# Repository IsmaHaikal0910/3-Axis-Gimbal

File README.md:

# Camera Gimbal — 3-Axis Stabilization for Smartphones & Cameras

> Custom-built 3-axis camera gimbal (STorM32 BGC + ESP32) with a self-designed 3D-printed frame, wireless shutter control, and a web dashboard for battery/BLE monitoring. Built for a Mechatronics lab project at Jade University of Applied Sciences.

---

## 🇬🇧 English

### Overview
This project is a fully custom 3-axis camera gimbal for smartphones and small action cameras, developed as part of the "Komplexlabor Mechatronik" course at Jade Hochschule Wilhelmshaven (Summer 2026). The goal was to design, build, and validate a handheld gimbal that stabilizes roll, pitch, and yaw in real time, using a mechanically optimized 3D-printed frame and an open, configurable electronics stack instead of a proprietary commercial system (e.g. DJI RS5).

### Key Features
- **3-axis active stabilization** (roll, pitch, yaw) via three iPower GM3506 brushless gimbal motors with AS5048A encoders
- **STorM32 v4.1** BGC controller + **NT IMU v4.2** for orientation sensing and PID-based motor control
- **ESP32** microcontroller handling joystick input, buttons, status LED, and wireless connectivity
- **WLAN/Bluetooth bridge**: a companion phone connects to the ESP32 over Wi-Fi and relays Bluetooth shutter commands to the camera
- **Custom HTML web interface** showing live battery percentage/voltage and providing remote shutter + Bluetooth scan controls
- Self-designed 3D-printed frame (P430 ABS+), removable 11.1 V / 3000 mAh LiPo battery, IP54-rated enclosure target
- Requirements list, circuit diagram, energy-flow diagram, and full verification & validation (V&V) test protocol

### Test Results (summary)
| Test | Result |
|---|---|
| Battery life (215 g payload) | ~2 hours |
| Reaction time (90° step) | 2.46 s (≈36.6°/s) |
| IMU drift (roll/pitch) | No measurable drift |
| Motor thermal | Uncritical after 10–15 min continuous load |
| TRL | 4, approaching 5 |

### Hardware
STorM32 v4.1, NT IMU v4.2, 3× iPower GM3506 gimbal motors, ESP32 (NodeMCU), analog joystick module, 2-button module, RGB status LED, 11.1 V 3000 mAh LiPo + balance charger. Full bill of materials with suppliers and cost is included in the lab report.

### Status & Outlook
The mechanical and electrical integration is complete; PID tuning (especially on the yaw axis) and full closed-loop real-time stabilization are ongoing. Planned next steps include C++/PlatformIO code refactoring with auto-reconnect, mechanical load testing of the screw connections, and empirical battery-life validation under real load.

---

## 🇩🇪 Deutsch

### Überblick
Dieses Projekt ist ein vollständig selbst entwickeltes 3-Achsen-Kamera-Gimbal für Smartphones und kleine Actioncams, entstanden im Rahmen des Komplexlabors Mechatronik an der Jade Hochschule Wilhelmshaven (Sommersemester 2026). Ziel war die Konstruktion, der Aufbau und die Validierung eines Handheld-Gimbals, das Roll-, Pitch- und Yaw-Bewegungen in Echtzeit ausgleicht — mit einem mechanisch optimierten, selbst konstruierten 3D-Druck-Rahmen und einer offenen, konfigurierbaren Elektronik statt eines proprietären kommerziellen Systems (z. B. DJI RS5).

### Hauptmerkmale
- **Aktive 3-Achsen-Stabilisierung** (Roll, Pitch, Yaw) über drei bürstenlose iPower-GM3506-Kardanmotoren mit AS5048A-Encodern
- **STorM32 v4.1** BGC-Controller + **NT IMU v4.2** zur Lageerfassung und PID-basierten Motorregelung
- **ESP32**-Mikrocontroller für Joystick-Eingabe, Taster, Status-LED und drahtlose Kommunikation
- **WLAN/Bluetooth-Brücke**: Ein Mobiltelefon verbindet sich per WLAN mit dem ESP32 und leitet Bluetooth-Auslösebefehle an die Kamera weiter
- **Eigenes HTML-Web-Interface** mit Live-Anzeige von Akkustand/Spannung sowie Fernsteuerung von Auslöser und Bluetooth-Suchlauf
- Selbst konstruierter 3D-Druck-Rahmen (P430 ABS+), entnehmbarer 11,1 V / 3000 mAh LiPo-Akku, Gehäuse ausgelegt auf IP54
- Anforderungsliste, Schaltplan, Energieflussdiagramm sowie ein vollständiges Verifikations- und Validierungs-Testprotokoll (V+V)

### Testergebnisse (Zusammenfassung)
| Test | Ergebnis |
|---|---|
| Akkulaufzeit (215 g Nutzlast) | ca. 2 Stunden |
| Reaktionszeit (90°-Schwenk) | 2,46 s (≈36,6°/s) |
| IMU-Drift (Roll/Pitch) | Keine messbare Drift |
| Motorerwärmung | Unkritisch nach 10–15 Min Dauerbetrieb |
| TRL | 4, an der Schwelle zu 5 |

### Hardware
STorM32 v4.1, NT IMU v4.2, 3× iPower-GM3506-Kardanmotoren, ESP32 (NodeMCU), analoges Joystick-Modul, 2-Tasten-Modul, RGB-Status-LED, 11,1 V 3000 mAh LiPo-Akku mit Balance-Ladegerät. Die vollständige Stückliste mit Lieferanten und Kosten befindet sich im Laborbericht.

### Status & Ausblick
Der mechanische und elektronische Aufbau ist abgeschlossen; die PID-Feinabstimmung (insbesondere der Yaw-Achse) sowie die vollständige Echtzeit-Stabilisierung im geschlossenen Regelkreis sind noch in Arbeit. Geplante nächste Schritte: Code-Refactoring in C++/PlatformIO mit automatischer Wiederverbindung, mechanischer Belastungstest der Schraubverbindungen sowie empirische Validierung der Akkulaufzeit unter realer Last.

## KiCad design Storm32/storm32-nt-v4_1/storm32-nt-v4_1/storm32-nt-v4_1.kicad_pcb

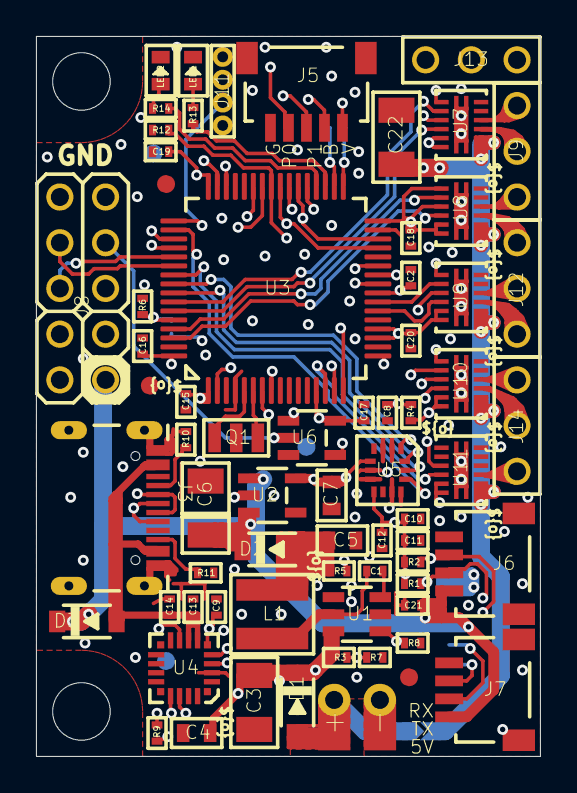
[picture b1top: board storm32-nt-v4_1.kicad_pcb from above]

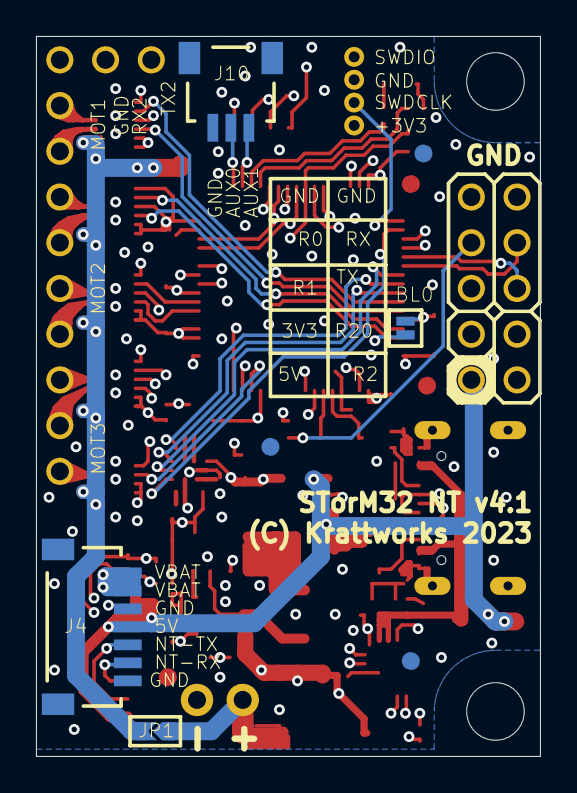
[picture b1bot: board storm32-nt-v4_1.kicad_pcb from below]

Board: 4 copper layers, 28.0 x 40.0 mm, 79 parts (7 on the bottom side), 69 nets.

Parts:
BL0: BOOT0; __SPARKFUN2_SJ_2S-NO
C1, C2, C8, C9, C11, C14, C16, C17, C18, C19, C20, C21: 0.1uF; 0402[1005-METRIC]
C3, C22: 10uF; 1206[3216-METRIC]
C4: 0.1uF; 0603[1608-METRIC]
C5, C7: 10uF; 0603[1608-METRIC]
C6: 100uF; 1206[3216-METRIC]-POL
C10: 2.2uF; 0402[1005-METRIC]
C12: 10nF; 0402[1005-METRIC]
C13, C15: 4.7uF; 0402[1005-METRIC]
D1, D2, D3: PMEG3010ER; SOD-123
FIDUCIAL1, FIDUCIAL2, FIDUCIAL3, FIDUCIAL4, FIDUCIAL5, FIDUCIAL6: FIDUCIAL
FRAMEBRD1: A5L-LOC
J1: +; 1
J2: -; 1
J3: TYPE-C-16P
J4: SM07B-SRSS-TB
J5: SM05B-SRSS-TB
J6, J7: SM04B-SRSS-TB
J8: HEADER; 2X5
J9, J12, J13, J14: HEADER_THT_2.54X1N_MALE-03
J10: SM03B-SRSS-TB
J11: HEADER_THT_1.27X1N_MALE-04
JP1: N/A; 0603[1608-METRIC]-0OHM-OFF
L1: 10uH; 4X4
LED1: GREEN; 0603[1608-METRIC]-DIODE
LED2: RED; 0603[1608-METRIC]-DIODE
Q1: 8MHz; RESONATOR
R1, R2, R13: 2k2; 0402[1005-METRIC]
R3: 15k; 0402[1005-METRIC]
R4, R6, R8, R9, R12: 10k; 0402[1005-METRIC]
R5: 75k; 0402[1005-METRIC]
R7: 1k5; 0402[1005-METRIC]
R10, R11: 5k1; 0402[1005-METRIC]
R14: 4k7; 0402[1005-METRIC]
U1: TPS54302; SOT-23-6
U2: XC6210B332MR; SOT-23-5
U3: STM32F103RCT6; QFP50P1200X1200X160-64N
U4: CP2102N; QFN-20
U5: ICM42688; LGA14
U6: 74AHC1G86; SOT-23-5
U7, U8, U9, U10, U11: DRV8839; WSON12
UNK_HOLE_0: dummyfp0
UNK_HOLE_1: dummyfp1

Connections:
+3V3: BL0.2, C7.P$1, C10.P$1, C11.P$1, C12.P$1, C15.P$1, C16.P$1, C17.P$1, C18.P$1, C19.P$1, C20.P$1, J5.1, J8.8, J11.1, R1.P$1, R2.P$1, R4.P$2, U2.5, U3.1, U3.13, U3.19, U3.20, U3.32, U3.48, U3.64, U5.5, U5.8, U6.5, U7.7, U7.9, U7.11, U7.12, U8.7, U8.9, U8.11, U8.12, U9.7, U9.9, U9.11, U9.12, U10.7, U10.9, U10.11, U10.12, U11.9, U11.11, U11.12
+5V: C6.P, C21.P$1, D2.C, D3.C, J4.4, J6.1, J7.1, J8.10, U2.1, U2.3
/CS: U3.50, U5.12
AUX0: J10.2, U3.33
AUX1: J10.1, U3.34
BUT: J5.2, U3.25
GND: C2.P$2, C3.P$2, C4.P$2, C5.P$2, C6.N, C7.P$2, C8.P$2, C9.P$2, C10.P$2, C11.P$2, C12.P$2, C13.P$2, C14.P$2, C15.P$2, C16.P$2, C17.P$2, C18.P$2, C19.P$2, C20.P$2, C21.P$2, C22.P$2, J2.1, J2.1A, J3.A1, J3.A12, J3.B1, J3.B12, J3.G1, J3.G2, J3.G3, J3.G4, J4.3, J4.7, J4.FIT@1, J4.FIT@2, J5.5, J5.FIT@1, J5.FIT@2, J6.4, J6.FIT@1, J6.FIT@2, J7.4, J7.FIT@1, J7.FIT@2, J8.1, J8.2, J10.3, J10.FIT@1, J10.FIT@2, J11.3, J13.1, LED1.C, LED2.C, Q1.G, R6.P$1, R7.P$1, R8.P$1, R10.P$2, R11.P$2, R12.P$2, U1.1, U2.2, U3.4, U3.12, U3.18, U3.28, U3.31, U3.47, U3.63, U4.3, U4.12, U5.2, U5.3, U5.6, U5.7, U5.10, U5.11, U6.3, U7.5, U7.6, U7.GND1, U7.GND2, U7.GND3, U7.GND4, U7.GND5, U8.5, U8.6, U8.GND1, U8.GND2, U8.GND3, U8.GND4, U8.GND5, U9.5, U9.6, U9.GND1, U9.GND2, U9.GND3, U9.GND4, U9.GND5, U10.5, U10.6, U10.GND1, U10.GND2, U10.GND3, U10.GND4, U10.GND5, U11.5, U11.6, U11.7, U11.8, U11.GND1, U11.GND2, U11.GND3, U11.GND4, U11.GND5
LED0: R13.P$2, U3.35
LED1: R14.P$2, U3.36
LIPO: C2.P$1, R3.P$1, R7.P$2, U3.24
M-A1: U3.58, U7.8
M-A2: U3.59, U7.10
M-A3: U3.61, U8.8
M-B1: U3.62, U8.10
M-B2: U3.23, U9.8
M-B3: U3.22, U9.10
M-C1: U3.26, U10.8
M-C2: U3.15, U10.10
M-C3: U3.14, U11.10
MISO: U3.56, U5.1
MOSI: U3.57, U5.14
unnamed: J3.A5, R10.P$1
unnamed: J3.B5, R11.P$1
unnamed: C1.P$1, L1.1, U1.2
unnamed: Q1.1, U3.6
unnamed: Q1.2, U3.5
unnamed: C8.P$1, R4.P$1, U3.7
unnamed: C1.P$2, U1.6
unnamed: LED1.A, R13.P$1
unnamed: J3.A6, J3.B6, U4.4
unnamed: J3.A7, J3.B7, U4.5
unnamed: C13.P$1, C14.P$1, D3.A, J3.A4, J3.A9, J3.B4, J3.B9, U4.7, U4.8
unnamed: R9.P$2, U4.9
unnamed: R5.P$1, R8.P$2, U1.4
unnamed: C22.P$1, JP1.P$2, U7.1, U7.2, U8.1, U8.2, U9.1, U9.2, U10.1, U10.2, U11.1, U11.2
unnamed: C5.P$1, D2.A, L1.2, R5.P$2
unnamed: LED2.A, R14.P$1
unnamed: J9.1, U7.4
unnamed: J9.2, U7.3
unnamed: J9.3, U8.4
unnamed: J12.1, U8.3
unnamed: J12.2, U9.4
unnamed: J12.3, U9.3
unnamed: J14.2, U10.3
unnamed: J14.1, U10.4
unnamed: BL0.1, R6.P$2, U3.60
unnamed: J14.3, U11.3
NT_RX: J4.6, J6.3, J7.3, R2.P$2, U3.52
NT_TX: J4.5, J6.2, J7.2, R1.P$2, U3.51
POT0: J5.4, U3.27
POT1: J5.3, U3.8
RC0/RX3: U3.30, U3.38, U6.4
RC2-0: J8.7, U3.39
RC-0: J8.4, U6.2
RC-1: J8.6, U3.29, U3.40
RC-2: J8.9, U3.37
RX1: U3.43, U4.18
RX2: J13.2, U3.17
RX5: J8.3, U3.54
SCK: U3.55, U5.13
SWC: J11.2, U3.49
SWD: J11.4, U3.46
TX1: U3.42, U4.17
TX2: J13.3, U3.16
TX5: J8.5, U3.53
USB_DETECT: C9.P$1, R9.P$1, U3.2, U4.6
VBAT: C3.P$1, C4.P$1, D1.C, J4.1, J4.2, R3.P$2, U1.3
VIN: D1.A, J1.1, J1.1A, JP1.P$1
XOR: R12.P$1, U3.41, U6.1
